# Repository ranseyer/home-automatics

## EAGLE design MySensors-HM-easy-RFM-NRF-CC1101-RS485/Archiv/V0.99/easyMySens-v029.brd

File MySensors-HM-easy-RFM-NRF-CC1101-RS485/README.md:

MySensors/HM easyPCB 

Communication via 
1) RFM69(H)W (868MHz and "W" Version recomended "HW" is not for all countries...), or 
2) CC1101 (868MHz for HomeMatic Protocol) 
3) NRF2401 (for mySensors 2,4 GHz) 
4) RS485 with Max487 for MySensors or Homematic Wired 

Connectors for 
1) N-Module Extensions 
2) Homematic-Universal PCB from Papa 
3) Grove Connectors but in 2,54mm raster 
4) Connector for screws or clamping 
5) more Sensors (I2C or Digital pin with Interupt) 
6) ATSHA204 (SMD solder)
 
Power via 
1) Step-Up 
2) Step-Down ("mini360")
3) Linear-Regulator 

Case 
1) Box2252
2) 59x65 (China Noname)
3) 67x98 (China Noname)
Many options with many drills 

Status 
Alpha, not tested. 

Important Hint:

Most Parts are optional. Use only what you need!

Changes / Known Bugs: 
-V01: 1 last-minute connection to "opt" header not knowingly not routed

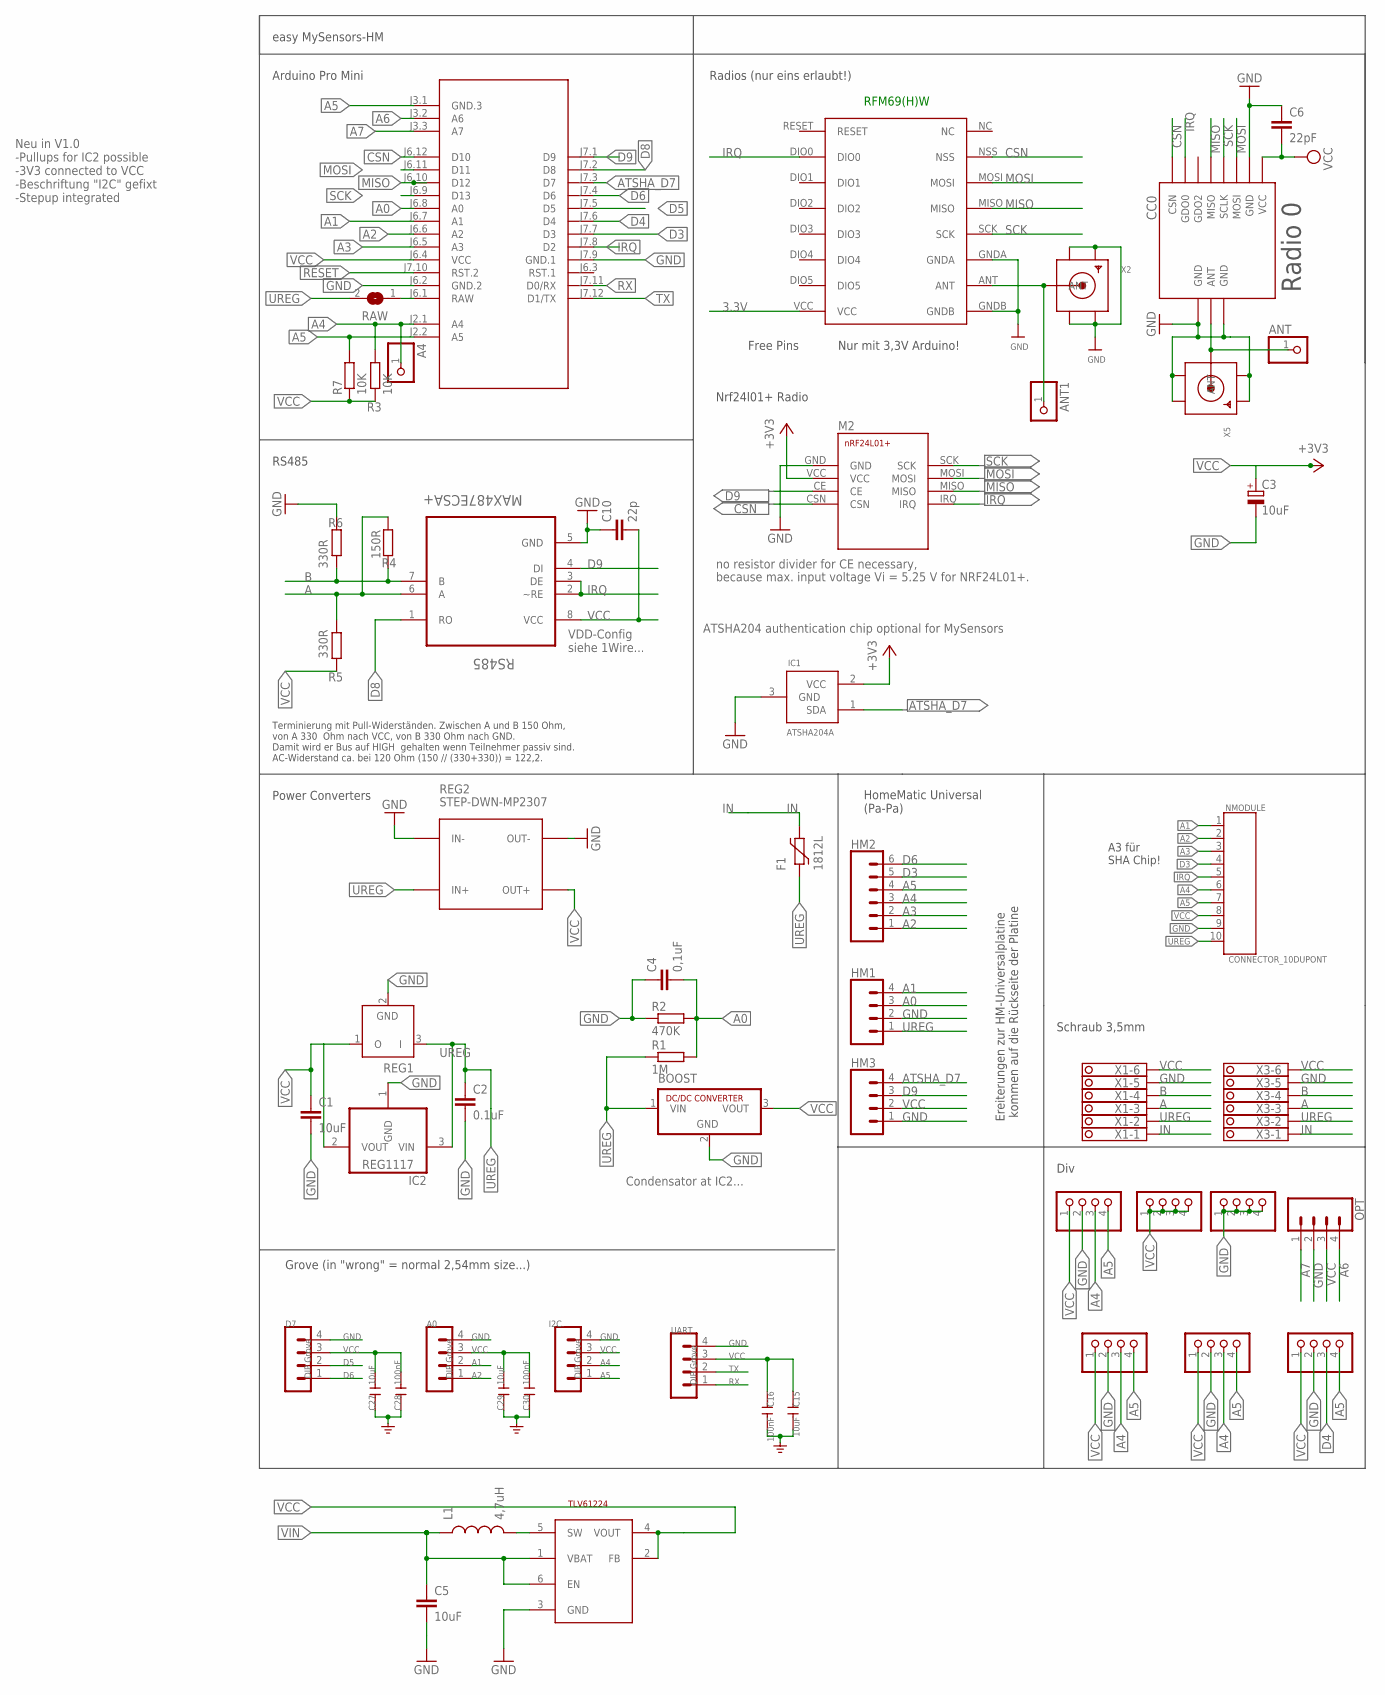
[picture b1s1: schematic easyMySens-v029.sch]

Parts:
A0: DIP Grove; MA04-1
A4: PINHD-1X1; 1X01
ANT, ANT1: PINHD-1X1; 1X01
BH1750: PINHD-1X04_2.54-S; 1X04-S
BOOST: R-78C1.8-1.0; SIP3
C1: 10uF; C1210
C2: 0.1uF; C1206
C3: 10uF; SMC_C
C4: 0,1uF; C1206
C5: 10uF; 0805
C6: 22pF; C0805
C10: 22p; C0805
C15, C27, C29: 10uF; C0603
C16, C28, C30: 100nF; C0603
CC0: CC1101; CC1101_MODULE1_SMD
D7: DIP Grove; MA04-1
F1: 1812L
HM1, HM3: CONN_04; 1X04
HM2: CONN_06SILK_FEMALE_PTH; 1X06
I2C-1, I2C-2: PINHD-1X04_2.54-S; 1X04-S
I2C.: DIP Grove; MA04-1
IC1: ATSHA204A; SOT23
IC2: REG1117; SOT223
JP1, JP3: PINHD-1X04_2.54-S; 1X04-S
L1: 4,7uH; 0805
M1: ARDUINO-PRO-MINI-3.3V#NP; ARDUINO-PRO-MINI#NP
M2: NRF24L01+SMD
MOTION: PINHD-1X04_2.54-S; 1X04-S
NMODULE: CONNECTOR_10DUPONT; DUPONT_10
OPT: CONN_04; 1X04
R1: 1M; R0805
R2: 470K; R0805
R3, R7: 10K; R0805
R4: 150R; R0805
R5, R6: 330R; R0805
RAW: SJ
REG1: LP2950Z; TO92
REG2: STEP-DWN-MP2307; DC-DC-STEP-DOWN-MP2307
RFM69W: RFM69HW; RFM
RS485: MAX487ECSA+; SOIC127P600X175-8N
STEPUP: TLV61224; SOT23-6L
UART: DIP Grove; MA04-1
X1, X3: 1751280
X2, X5: SMACONNECTOR_EDGE; SMA_EDGELAUNCH

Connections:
3.3V: IC1.2 (VCC), M2.VCC, RFM69W.VCC
A: R4.1, R5.2, RS485.6 (A), X1.3, X3.3
A0: C4.2, HM1.3, M1.J6.8 (A0), R1.2, R2.2
A1: A0.2, HM1.4, M1.J6.7 (A1), NMODULE.1
A2: A0.1, HM2.1, M1.J6.6 (A2), NMODULE.2
A3: HM2.2, M1.J6.5 (A3), NMODULE.3
A4: A4.1, BH1750.3, HM2.3, I2C-1.3, I2C-2.3, I2C..2, M1.J2.1 (A4), NMODULE.6, R3.2
A5: BH1750.4, HM2.4, I2C-1.4, I2C-2.4, I2C..1, M1.J2.2 (A5), M1.J3.1 (GND.3), MOTION.4, NMODULE.7, R7.2
A6: M1.J3.2 (A6), OPT.4
A7: M1.J3.3 (A7), OPT.1
ANT0: ANT.1, CC0.ANT, X5.P (ANT)
ATSHA_D7: HM3.4, IC1.1 (SDA), M1.J7.3 (D7)
B: R4.2, R6.1, RS485.7 (B), X1.4, X3.4
CSN: CC0.CSN, M1.J6.12 (D10), M2.CSN, RFM69W.NSS
D3: HM2.5, M1.J7.7 (D3), NMODULE.4
D4: M1.J7.6 (D4), MOTION.3
D5: D7.2, M1.J7.5 (D5)
D6: D7.1, HM2.6, M1.J7.4 (D6)
D8: M1.J7.2 (D8), RS485.1 (RO)
D9: HM3.3, M1.J7.1 (D9), M2.CE, RS485.4 (DI)
GND: A0.4, BH1750.2, BOOST.2 (GND), C1.2, C2.2, C3.-, C4.1, C5.2, C6.1, C10.1, C15.1, C16.1, C27.2, C28.2, C29.2, C30.2, CC0.GND@0 (GND), CC0.GND@1 (GND), CC0.GND@2 (GND), D7.4, HM1.2, HM3.1, I2C-1.2, I2C-2.2, I2C..4, IC1.3 (GND), IC2.1 (GND), JP1.1, JP1.2, JP1.3, JP1.4, M1.J6.2 (GND.2), M1.J7.9 (GND.1), M2.GND, MOTION.2, NMODULE.9, OPT.2, R2.1, R6.2, REG1.2 (GND), REG2.IN-, REG2.OUT-, RFM69W.GNDA, RFM69W.GNDB, RS485.5 (GND), STEPUP.3 (GND), UART.4, X1.5, X2.GND@1 (GND4), X2.GND@2 (GND3), X2.GND@3 (GND2), X2.GND@4 (GND1), X3.5, X5.GND@1 (GND4), X5.GND@2 (GND3), X5.GND@3 (GND2), X5.GND@4 (GND1)
IN: F1.P$2 (2), X1.1, X3.1
IRQ: CC0.GDO0, M1.J7.8 (D2), M2.IRQ, NMODULE.5, RFM69W.DIO0, RS485.2 (~RE), RS485.3 (DE)
MISO: CC0.MISO, M1.J6.10 (D12), M2.MISO, RFM69W.MISO
MOSI: CC0.MOSI, M1.J6.11 (D11), M2.MOSI, RFM69W.MOSI
unnamed: L1.2, STEPUP.5 (SW)
unnamed: ANT1.1, RFM69W.ANT, X2.P (ANT)
RAW: M1.J6.1 (RAW), RAW.1
RESET: M1.J7.10 (RST.2)
RX: M1.J7.11 (D0/RX), UART.1
SCK: CC0.SCLK, M1.J6.9 (D13), M2.SCK, RFM69W.SCK
TX: M1.J7.12 (D1/TX), UART.2
UREG: BOOST.1 (VIN), C2.1, F1.P$1 (1), HM1.1, IC2.3 (VIN), NMODULE.10, R1.1, RAW.2, REG1.3 (I), REG2.IN+, X1.2, X3.2
VCC: A0.3, BH1750.1, BOOST.3 (VOUT), C1.1, C3.+, C6.2, C10.2, C15.2, C16.2, C27.1, C28.1, C29.1, C30.1, CC0.VCC, D7.3, HM3.2, I2C-1.1, I2C-2.1, I2C..3, IC2.2 (VOUT), JP3.1, JP3.2, JP3.3, JP3.4, M1.J6.4 (VCC), MOTION.1, NMODULE.8, OPT.3, R3.1, R5.1, R7.1, REG1.1 (O), REG2.OUT+, RS485.8 (VCC), STEPUP.2 (FB), STEPUP.4 (VOUT), UART.3, X1.6, X3.6
VIN: C5.1, L1.1, STEPUP.1 (VBAT), STEPUP.6 (EN)

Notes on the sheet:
easy MySensors-HM
Arduino Pro Mini
Free Pins
Nrf24l01+ Radio
Power Converters
RS485
VDD-Config siehe 1Wire...
no resistor divider for CE necessary,
because max. input voltage Vi = 5.25 V for NRF24L01+.
ATSHA204 authentication chip optional for MySensors
RFM69(H)W
Nur mit 3,3V Arduino!
Radio 0
Terminierung mit Pull-Widerständen. Zwischen A und B 150 Ohm, von A 330 Ohm nach VCC, von B 330 Ohm nach GND. Damit wird er Bus auf HIGH gehalten wenn Teilnehmer passiv sind. AC-Widerstand ca. bei 120 Ohm (150 // (330+330)) = 122,2.
A3 für SHA Chip!
Ereiterungen zur HM-Universalplatine kommen auf die Rückseite der Platine
Condensator at IC2...
HomeMatic Universal (Pa-Pa)
Schraub 3,5mm
Div
Radios (nur eins erlaubt!)
Grove (in "wrong" = normal 2,54mm size...)
Neu in V1.0 -Pullups for IC2 possible -3V3 connected to VCC -Beschriftung "I2C" gefixt -Stepup integrated

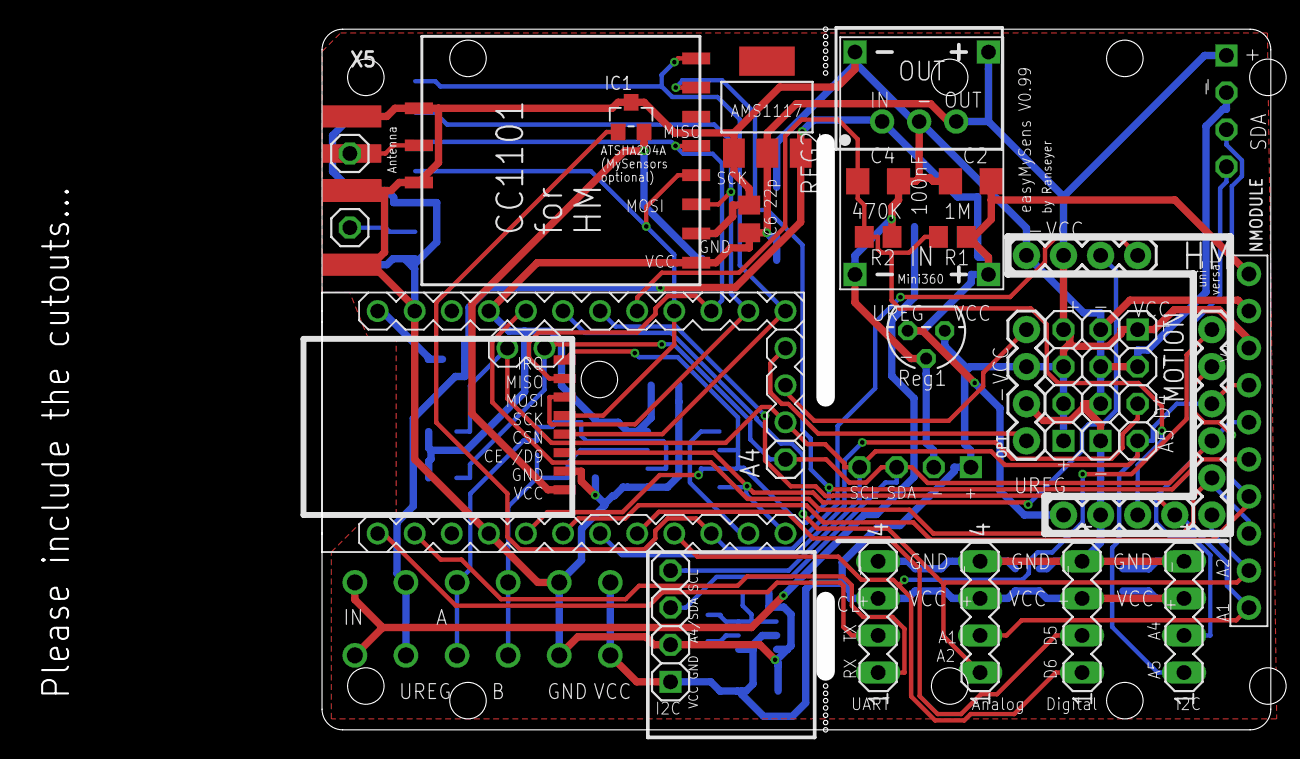
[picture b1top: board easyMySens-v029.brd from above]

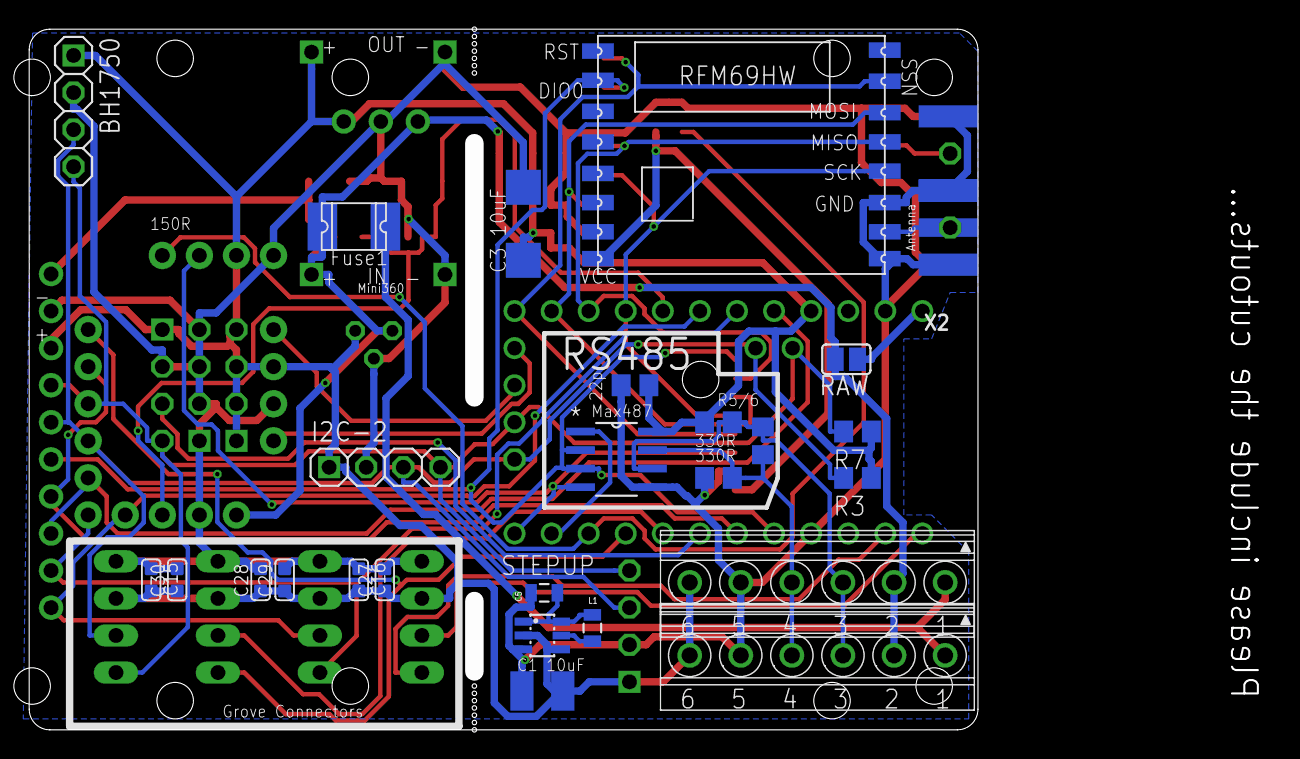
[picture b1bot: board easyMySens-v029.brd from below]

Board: 2 copper layers, 65.0 x 48.0 mm, 56 parts (26 on the bottom side), 34 nets.

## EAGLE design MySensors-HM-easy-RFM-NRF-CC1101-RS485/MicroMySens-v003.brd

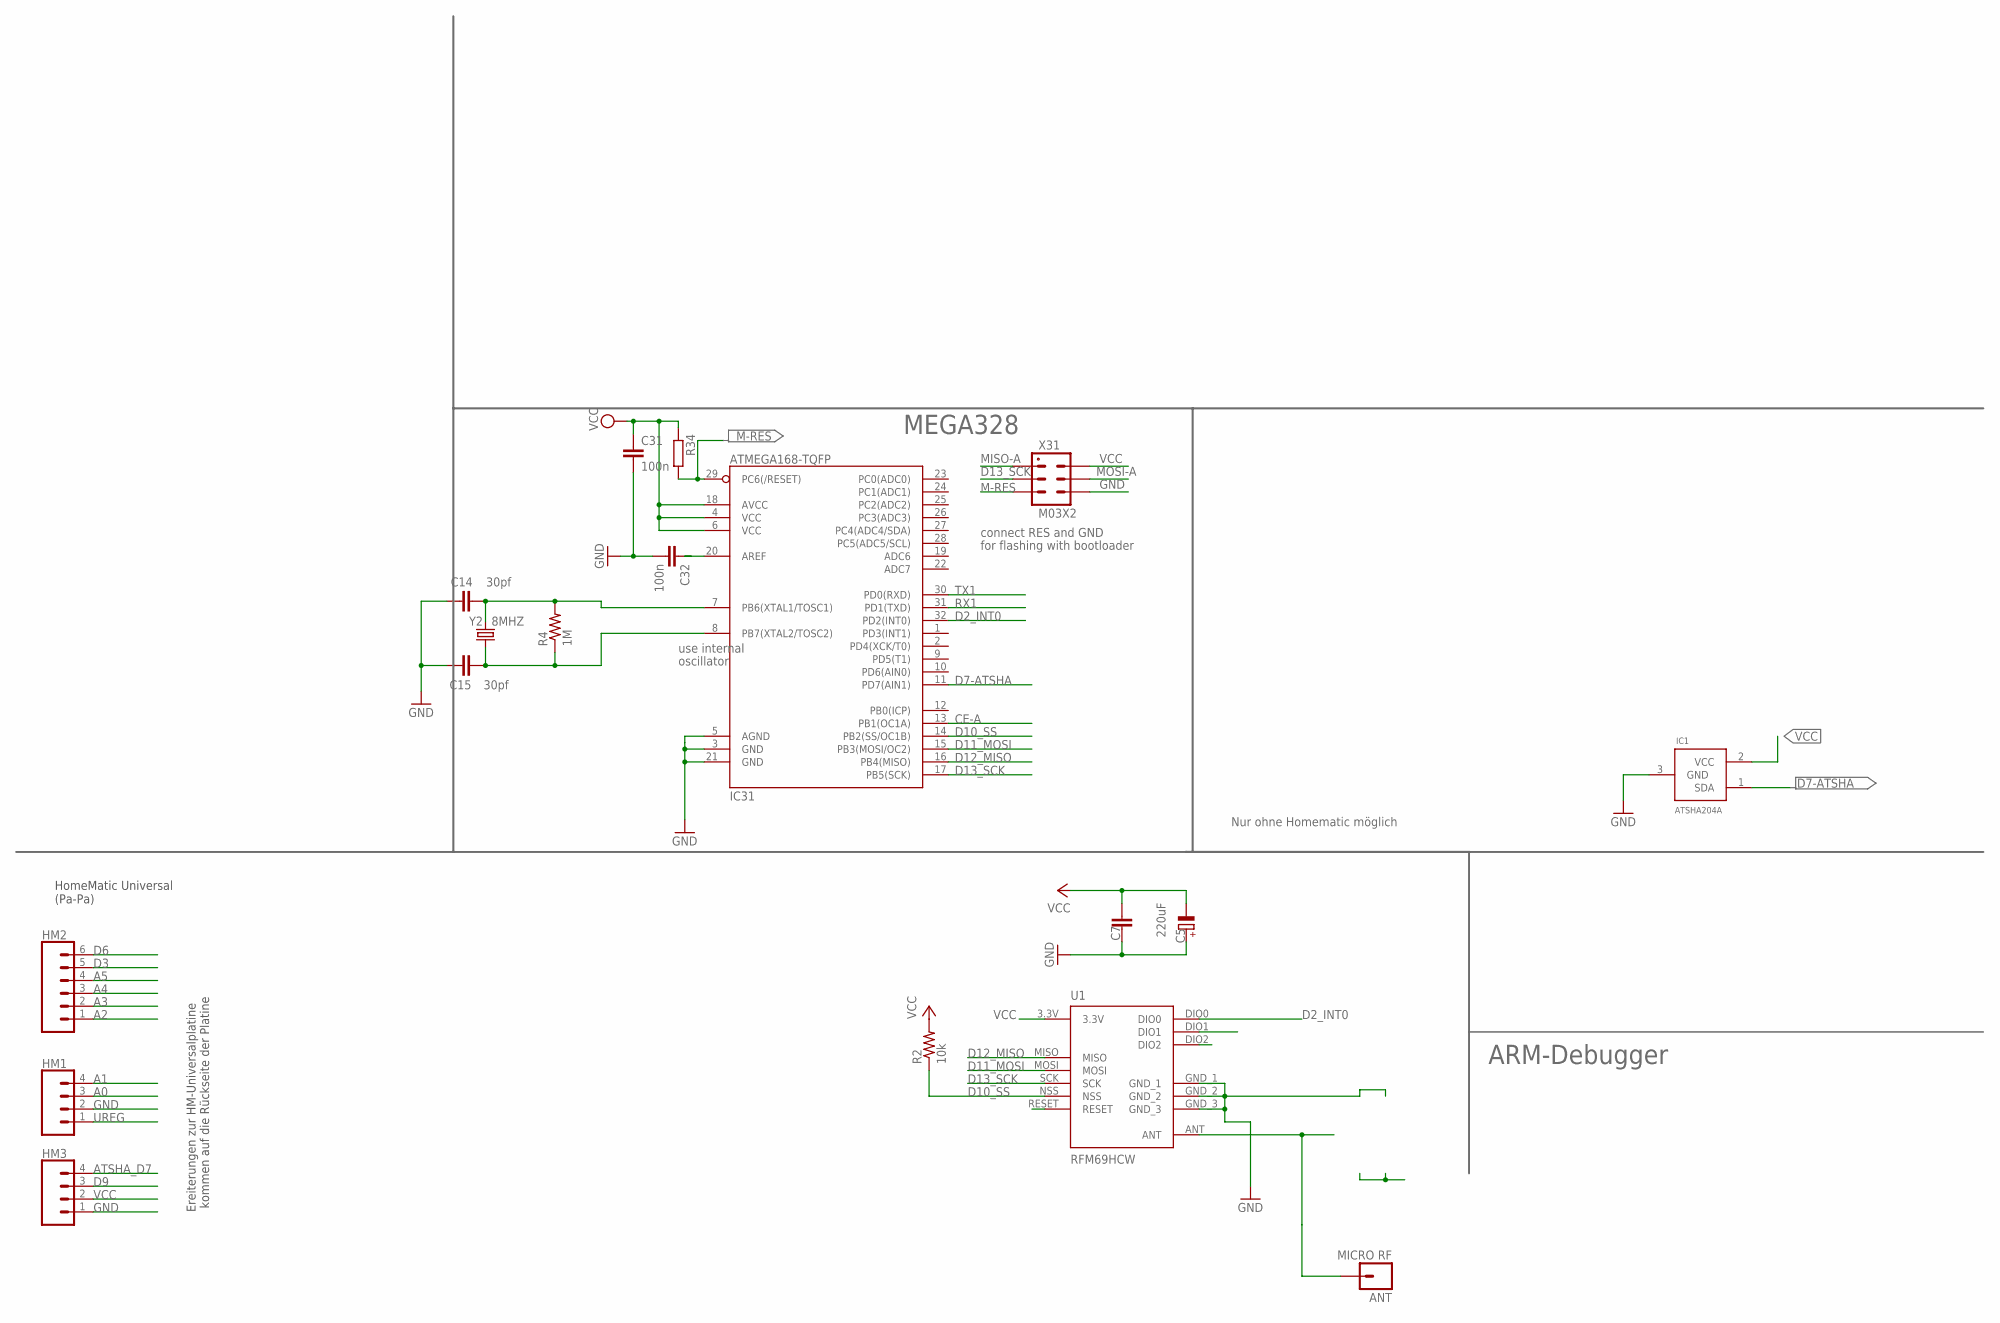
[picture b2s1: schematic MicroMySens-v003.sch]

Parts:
ANT: MICRO RF; 1X01
C5: 220uF; E5-8,5
C7: C-EUC1812; C1812
C14, C15: 30pf; 0805
C31, C32: 100n; C0805
HM1, HM3: CONN_04; 1X04
HM2: CONN_06SILK_FEMALE_PTH; 1X06
IC1: ATSHA204A; SOT23
IC31: ATMEGA168-TQFP; TQFP32-08
R2: 10k; 0805
R4: 1M; 0805
R34: R-EU_R0805; R0805
U1: RFM69HCW; RFM69HCW-XXXS2
X31: M03X2; 2X03-1.27MM_SMD
Y2: 8MHZ; CRYSTAL-TXC-7A

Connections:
A0: HM1.3
A1: HM1.4
A2: HM2.1
A3: HM2.2
A4: HM2.3
A5: HM2.4
ANT: ANT.1, U1.ANT
ATSHA_D7: HM3.4
CE-A: IC31.13 (PB1(OC1A))
D2_INT0: IC31.32 (PD2(INT0)), U1.DIO0
D3: HM2.5
D6: HM2.6
D7-ATSHA: IC1.1 (SDA), IC31.11 (PD7(AIN1))
D9: HM3.3
D10_SS: IC31.14 (PB2(SS/OC1B)), R2.1, U1.NSS
D11_MOSI: IC31.15 (PB3(MOSI/OC2)), U1.MOSI
D12_MISO: IC31.16 (PB4(MISO)), U1.MISO
D13_SCK: IC31.17 (PB5(SCK)), U1.SCK, X31.P$3 (3)
GND: C5.+, C7.2, C14.1, C15.1, C31.2, C32.2, HM1.2, HM3.1, IC1.3 (GND), IC31.3 (GND), IC31.5 (AGND), IC31.21 (GND), U1.GND_1, U1.GND_2, U1.GND_3, X31.P$6 (6)
M-RES: IC31.29 (PC6(/RESET)), R34.2, X31.P$5 (5)
MISO-A: X31.P$1 (1)
MOSI-A: X31.P$4 (4)
unnamed: C14.2, IC31.7 (PB6(XTAL1/TOSC1)), R4.2, Y2.P$2 (2)
unnamed: C32.1, IC31.20 (AREF)
unnamed: C15.2, IC31.8 (PB7(XTAL2/TOSC2)), R4.1, Y2.P$1 (1)
RX1: IC31.31 (PD1(TXD))
TX1: IC31.30 (PD0(RXD))
UREG: HM1.1
VCC: C5.-, C7.1, C31.1, HM3.2, IC1.2 (VCC), IC31.4 (VCC), IC31.6 (VCC), IC31.18 (AVCC), R2.2, R34.1, U1.3.3V, X31.P$2 (2)

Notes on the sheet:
MEGA328
ARM-Debugger
use internal
oscillator
connect RES and GND
for flashing with bootloader
Nur ohne Homematic möglich
Ereiterungen zur HM-Universalplatine kommen auf die Rückseite der Platine
HomeMatic Universal (Pa-Pa)

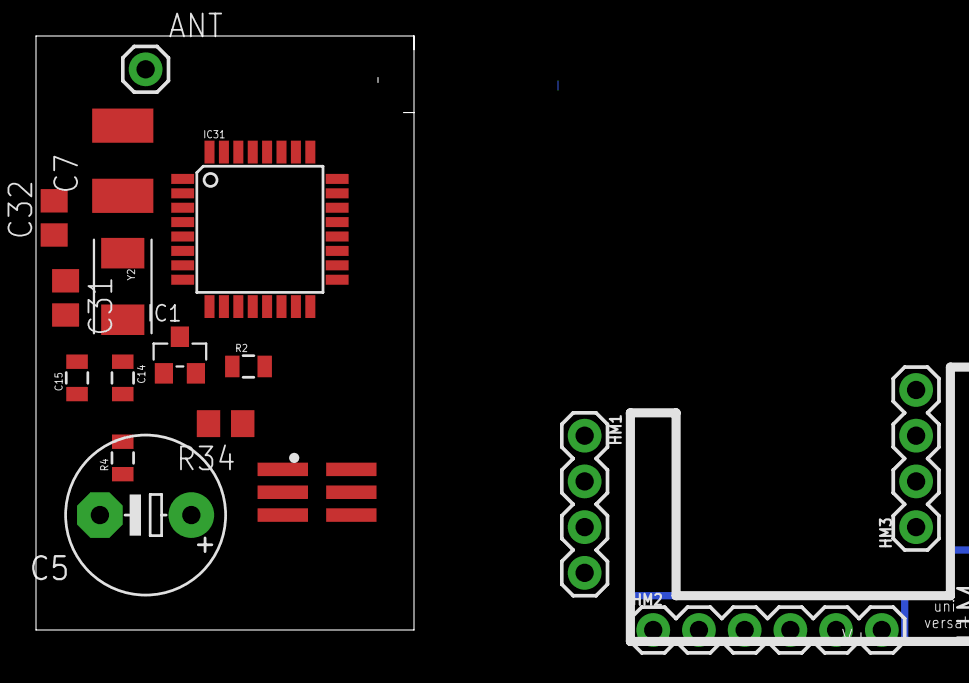
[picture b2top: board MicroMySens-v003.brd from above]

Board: 2 copper layers, 21.0 x 33.0 mm, 18 parts (1 on the bottom side), 13 nets.

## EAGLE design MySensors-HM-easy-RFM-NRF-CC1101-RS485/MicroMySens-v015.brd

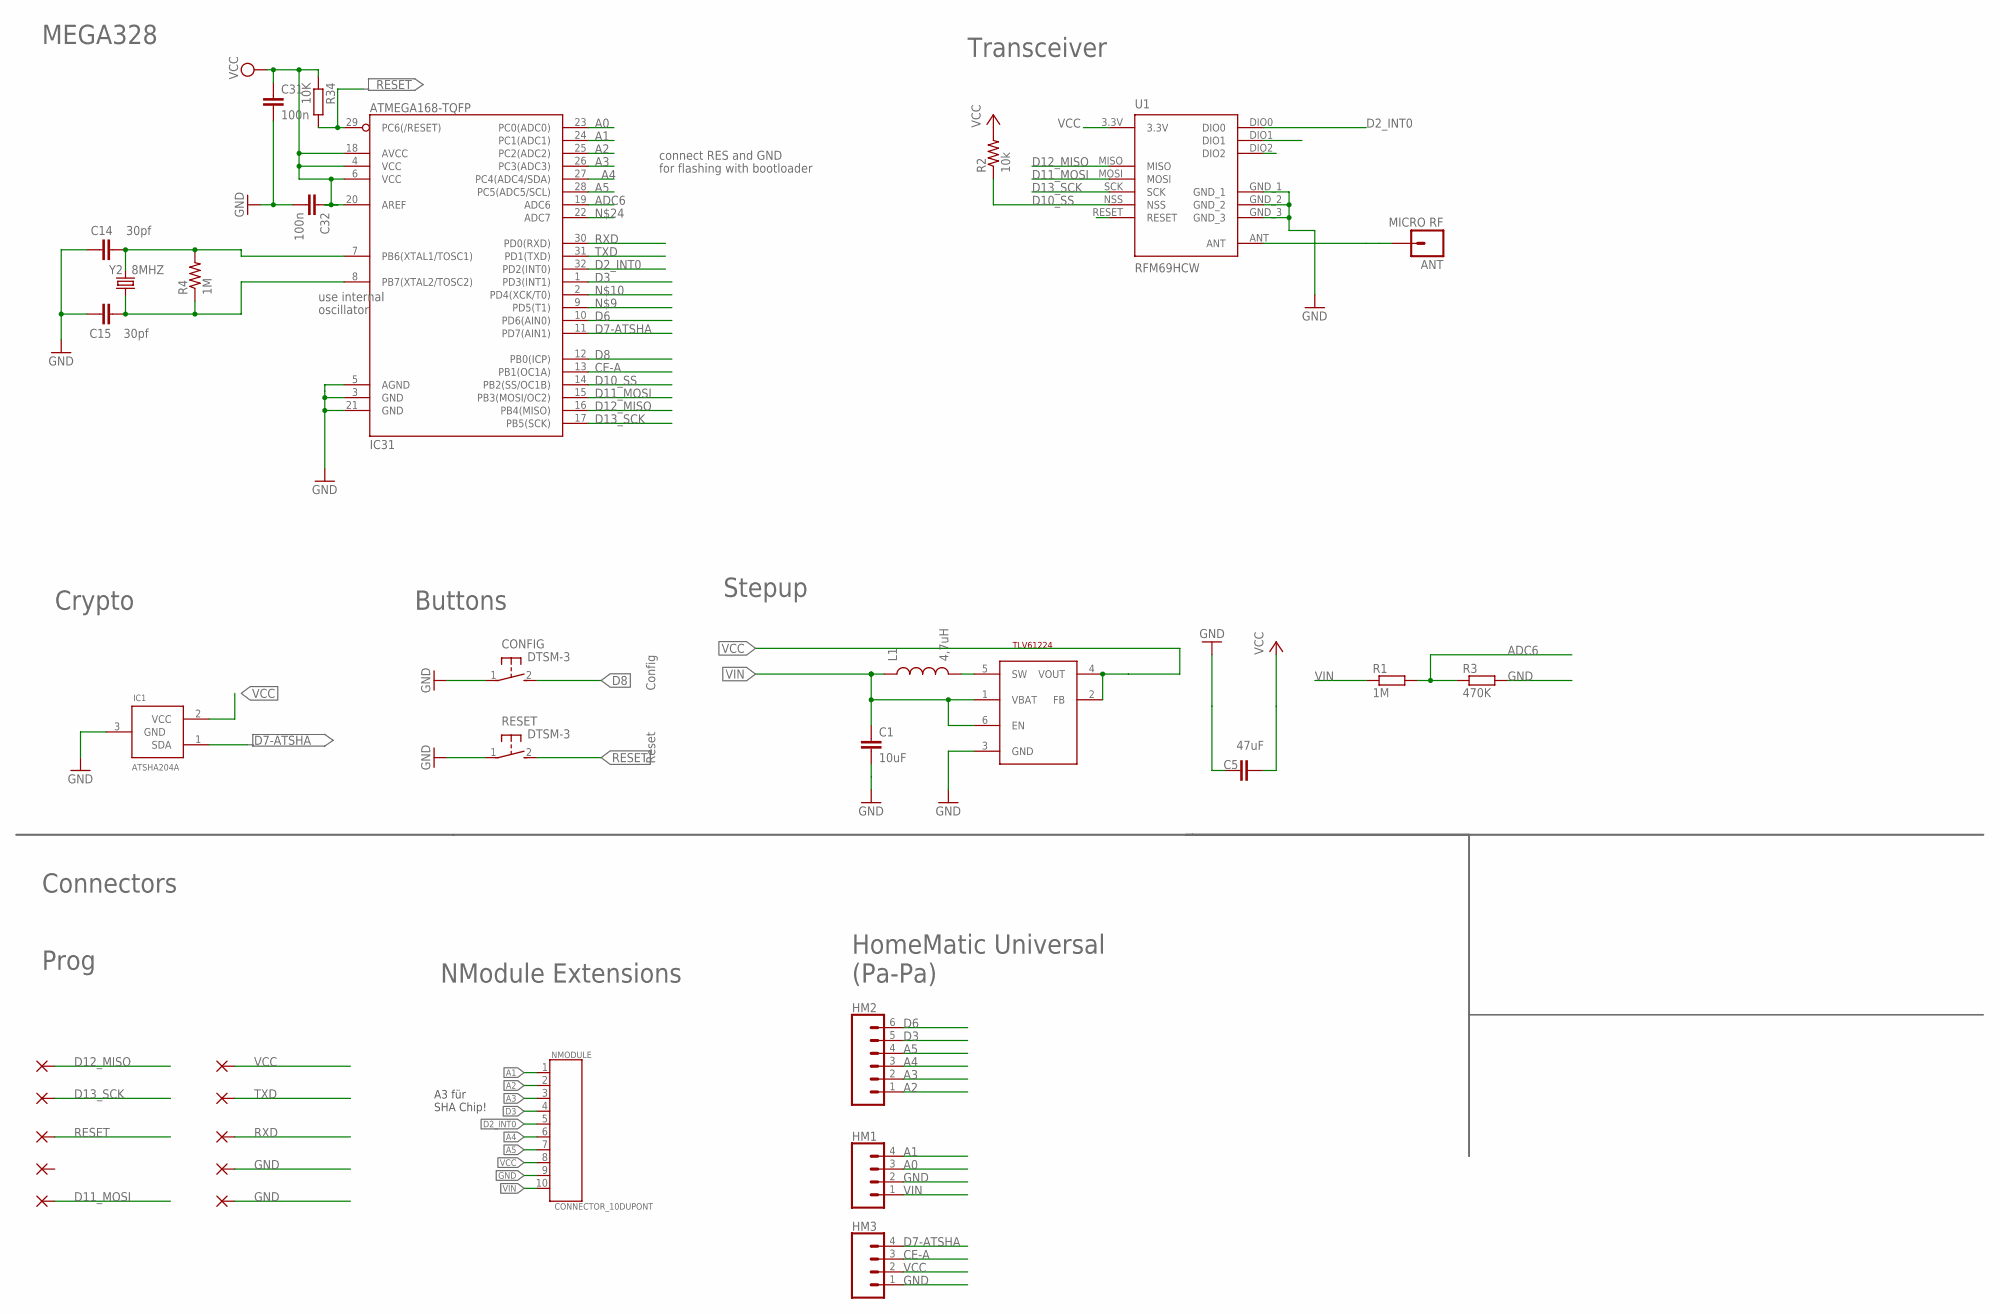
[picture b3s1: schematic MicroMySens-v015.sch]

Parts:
ANT: MICRO RF; 1X01
C1: 10uF; 0805
C5: 47uF; C1210
C14, C15: 30pf; 0805
C31, C32: 100n; C0805
CONFIG: DTSM-3
GND, GND2: WIREPADSMD1,27-254; SMD1,27-2,54
HM1, HM3: CONN_04; 1X04
HM2: CONN_06SILK_FEMALE_PTH; 1X06
IC1: ATSHA204A; SOT23
IC31: ATMEGA168-TQFP; TQFP32-08
L1: 4,7uH; 0805
MISO: WIREPADSMD1,27-254; SMD1,27-2,54
MOSI: WIREPADSMD1,27-254; SMD1,27-2,54
NC: WIREPADSMD1,27-254; SMD1,27-2,54
NMODULE: CONNECTOR_10DUPONT; DUPONT_10
R1: 1M; R0805
R2: 10k; 0805
R3: 470K; R0805
R4: 1M; 0805
R34: 10K; R0805
RESET: DTSM-3
RST: WIREPADSMD1,27-254; SMD1,27-2,54
RXD: WIREPADSMD1,27-254; SMD1,27-2,54
SCK: WIREPADSMD1,27-254; SMD1,27-2,54
STEPUP: TLV61224; SOT23-6L
TXD: WIREPADSMD1,27-254; SMD1,27-2,54
U1: RFM69HCW; RFM69HCW-XXXS2
VCC: WIREPADSMD1,27-254; SMD1,27-2,54
Y2: 8MHZ; CRYSTAL-TXC-7A

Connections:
A0: HM1.3, IC31.23 (PC0(ADC0))
A1: HM1.4, IC31.24 (PC1(ADC1)), NMODULE.1
A2: HM2.1, IC31.25 (PC2(ADC2)), NMODULE.2
A3: HM2.2, IC31.26 (PC3(ADC3)), NMODULE.3
A4: HM2.3, IC31.27 (PC4(ADC4/SDA)), NMODULE.6
A5: HM2.4, IC31.28 (PC5(ADC5/SCL)), NMODULE.7
ADC6: IC31.19 (ADC6), R1.2, R3.1
ANT: ANT.1, U1.ANT
CE-A: HM3.3, IC31.13 (PB1(OC1A))
D2_INT0: IC31.32 (PD2(INT0)), NMODULE.5, U1.DIO0
D3: HM2.5, IC31.1 (PD3(INT1)), NMODULE.4
D6: HM2.6, IC31.10 (PD6(AIN0))
D7-ATSHA: HM3.4, IC1.1 (SDA), IC31.11 (PD7(AIN1))
D8: CONFIG.2, IC31.12 (PB0(ICP))
D10_SS: IC31.14 (PB2(SS/OC1B)), R2.1, U1.NSS
D11_MOSI: IC31.15 (PB3(MOSI/OC2)), MOSI.1, U1.MOSI
D12_MISO: IC31.16 (PB4(MISO)), MISO.1, U1.MISO
D13_SCK: IC31.17 (PB5(SCK)), SCK.1, U1.SCK
GND: C1.2, C5.1, C14.1, C15.1, C31.2, C32.2, CONFIG.1, GND.1, GND2.1, HM1.2, HM3.1, IC1.3 (GND), IC31.3 (GND), IC31.5 (AGND), IC31.21 (GND), NMODULE.9, R3.2, RESET.1, STEPUP.3 (GND), U1.GND_1, U1.GND_2, U1.GND_3
unnamed: C14.2, IC31.7 (PB6(XTAL1/TOSC1)), R4.2, Y2.P$2 (2)
unnamed: L1.2, STEPUP.5 (SW)
unnamed: C15.2, IC31.8 (PB7(XTAL2/TOSC2)), R4.1, Y2.P$1 (1)
RESET: IC31.29 (PC6(/RESET)), R34.2, RESET.2, RST.1
RXD: IC31.30 (PD0(RXD)), RXD.1
TXD: IC31.31 (PD1(TXD)), TXD.1
VCC: C5.2, C31.1, C32.1, HM3.2, IC1.2 (VCC), IC31.4 (VCC), IC31.6 (VCC), IC31.18 (AVCC), IC31.20 (AREF), NMODULE.8, R2.2, R34.1, STEPUP.2 (FB), STEPUP.4 (VOUT), U1.3.3V, VCC.1
VIN: C1.1, HM1.1, L1.1, NMODULE.10, R1.1, STEPUP.1 (VBAT), STEPUP.6 (EN)

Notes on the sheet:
MEGA328
use internal
oscillator
connect RES and GND
for flashing with bootloader
A3 für SHA Chip!
Config
Reset
Crypto
Buttons
Stepup
Transceiver
Connectors
Prog
NModule Extensions
HomeMatic Universal (Pa-Pa)

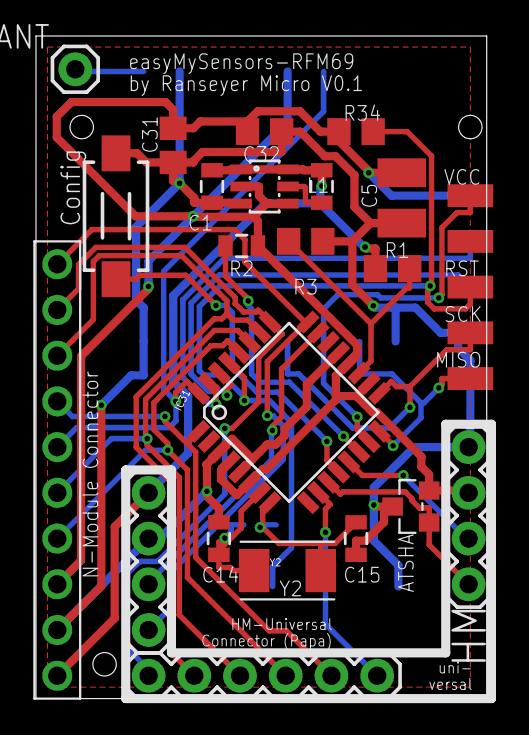
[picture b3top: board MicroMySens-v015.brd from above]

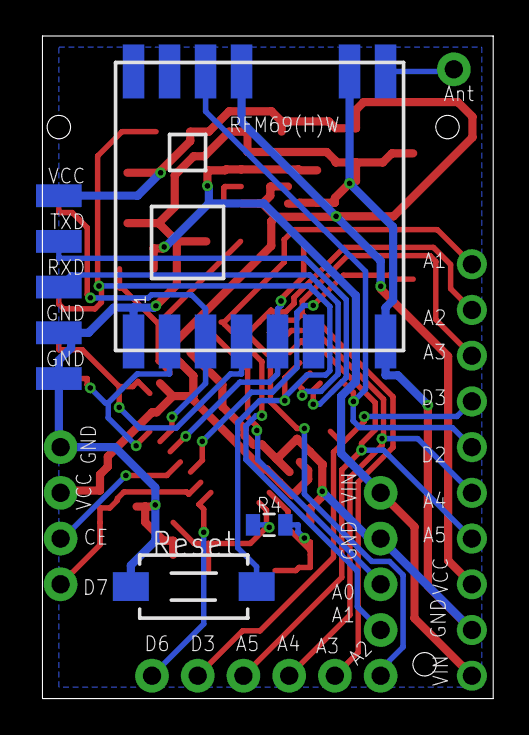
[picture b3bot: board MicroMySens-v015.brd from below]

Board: 2 copper layers, 25.0 x 36.8 mm, 34 parts (8 on the bottom side), 27 nets.

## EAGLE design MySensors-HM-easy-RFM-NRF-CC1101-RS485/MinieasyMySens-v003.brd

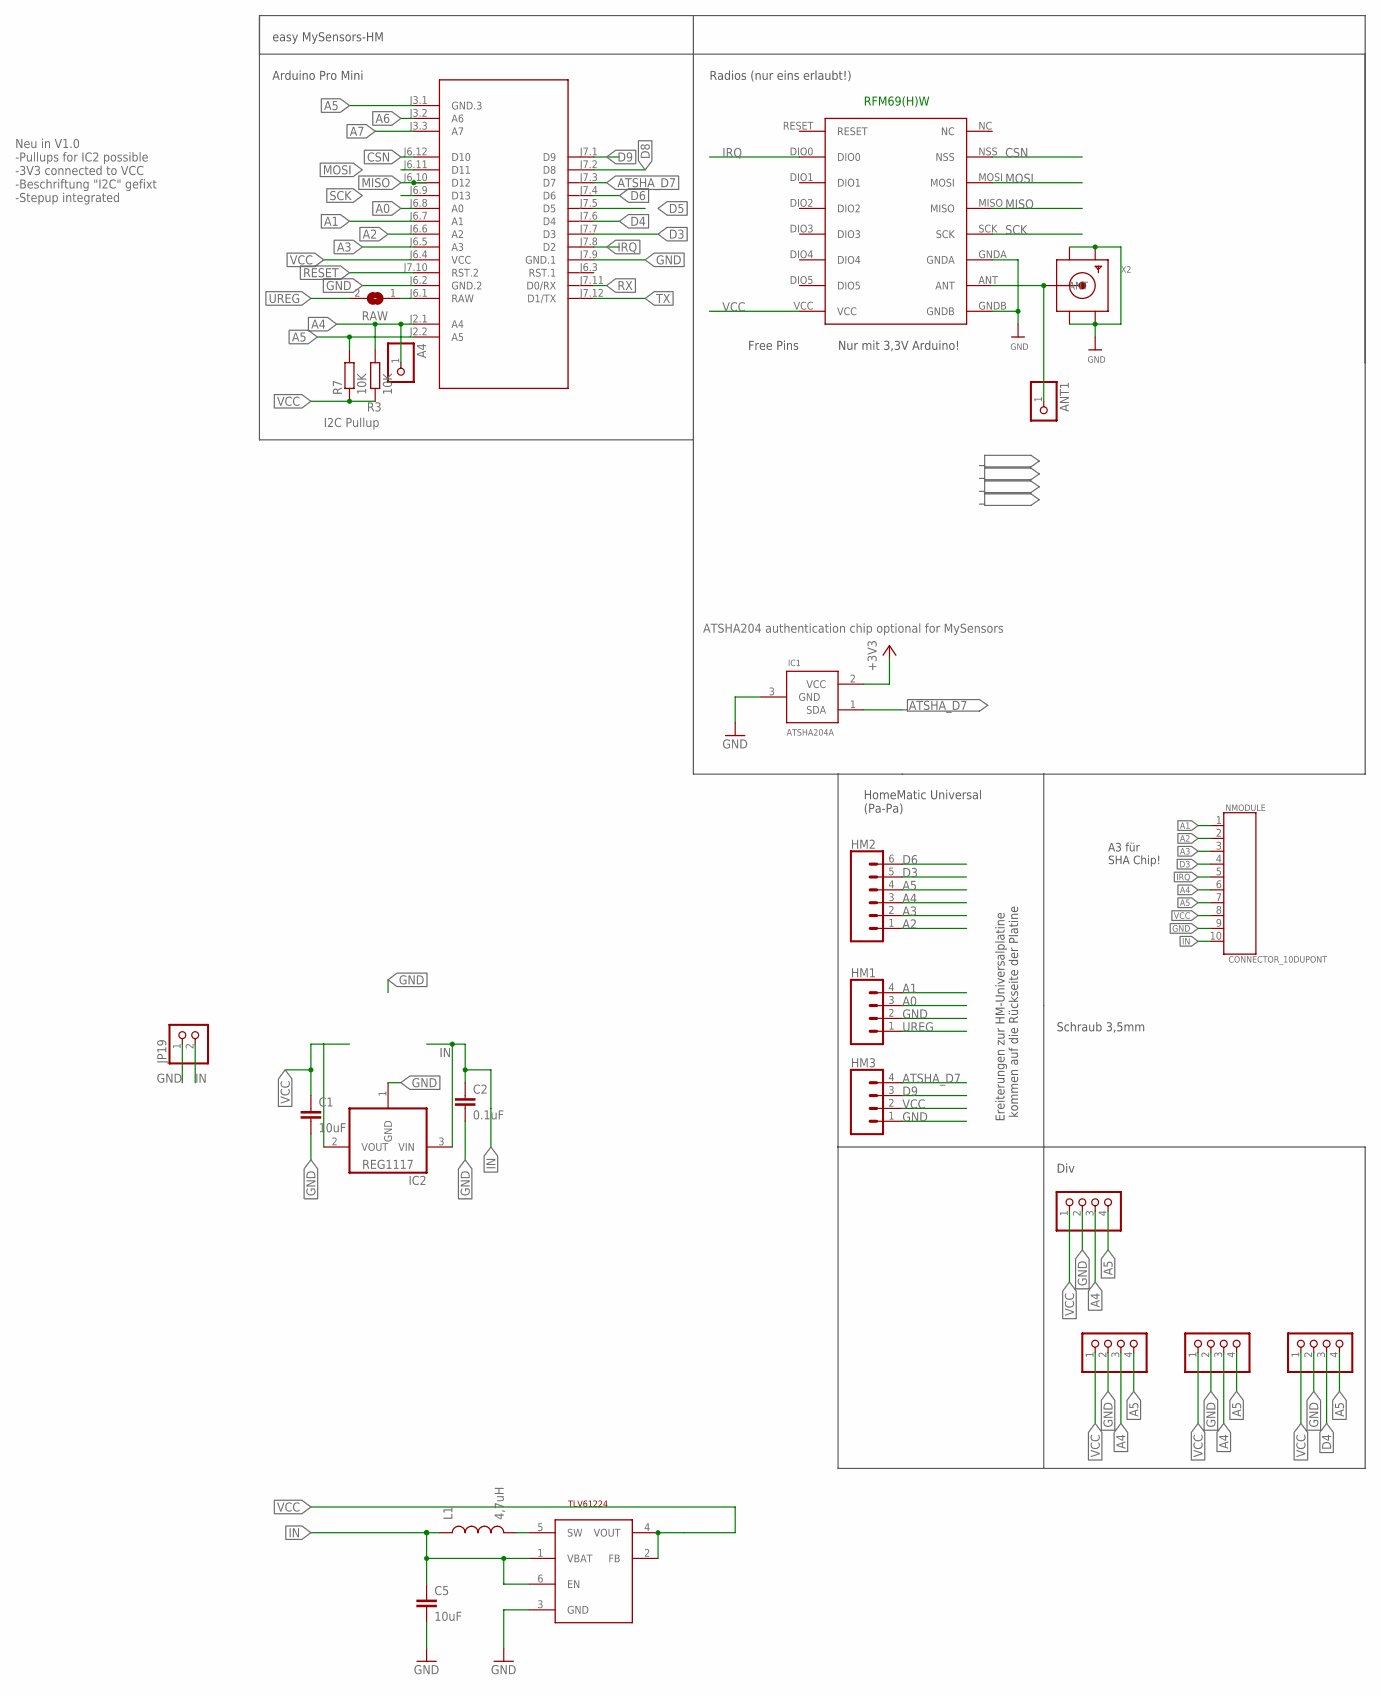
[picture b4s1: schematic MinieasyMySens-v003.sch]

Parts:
A4: PINHD-1X1; 1X01
ANT1: PINHD-1X1; 1X01
BH1750: PINHD-1X04_2.54-S; 1X04-S
C1: 10uF; C1210
C2: 0.1uF; C1206
C5: 10uF; 0805
HM1, HM3: CONN_04; 1X04
HM2: CONN_06SILK_FEMALE_PTH; 1X06
I2C-1, I2C-2: PINHD-1X04_2.54-S; 1X04-S
IC1: ATSHA204A; SOT23
IC2: REG1117; SOT223
JP19: PINHD-1X2; 1X02
L1: 4,7uH; 0805
M1: ARDUINO-PRO-MINI-3.3V#NP; ARDUINO-PRO-MINI#NP
MOTION: PINHD-1X04_2.54-S; 1X04-S
NMODULE: CONNECTOR_10DUPONT; DUPONT_10
R3, R7: 10K; R0805
RAW: SJ
RFM69W: RFM69HW; RFM
STEPUP: TLV61224; SOT23-6L
X2: SMACONNECTOR_EDGE; SMA_EDGELAUNCH

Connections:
A0: HM1.3, M1.J6.8 (A0)
A1: HM1.4, M1.J6.7 (A1), NMODULE.1
A2: HM2.1, M1.J6.6 (A2), NMODULE.2
A3: HM2.2, M1.J6.5 (A3), NMODULE.3
A4: A4.1, BH1750.3, HM2.3, I2C-1.3, I2C-2.3, M1.J2.1 (A4), NMODULE.6, R3.2
A5: BH1750.4, HM2.4, I2C-1.4, I2C-2.4, M1.J2.2 (A5), M1.J3.1 (GND.3), MOTION.4, NMODULE.7, R7.2
A6: M1.J3.2 (A6)
A7: M1.J3.3 (A7)
ATSHA_D7: HM3.4, IC1.1 (SDA), M1.J7.3 (D7)
CSN: M1.J6.12 (D10), RFM69W.NSS
D3: HM2.5, M1.J7.7 (D3), NMODULE.4
D4: M1.J7.6 (D4), MOTION.3
D5: M1.J7.5 (D5)
D6: HM2.6, M1.J7.4 (D6)
D8: M1.J7.2 (D8)
D9: HM3.3, M1.J7.1 (D9)
GND: BH1750.2, C1.2, C2.2, C5.2, HM1.2, HM3.1, I2C-1.2, I2C-2.2, IC1.3 (GND), IC2.1 (GND), JP19.1, M1.J6.2 (GND.2), M1.J7.9 (GND.1), MOTION.2, NMODULE.9, RFM69W.GNDA, RFM69W.GNDB, STEPUP.3 (GND), X2.GND@1 (GND4), X2.GND@2 (GND3), X2.GND@3 (GND2), X2.GND@4 (GND1)
IN: C2.1, C5.1, IC2.3 (VIN), JP19.2, L1.1, NMODULE.10, STEPUP.1 (VBAT), STEPUP.6 (EN)
IRQ: M1.J7.8 (D2), NMODULE.5, RFM69W.DIO0
MISO: M1.J6.10 (D12), RFM69W.MISO
MOSI: M1.J6.11 (D11), RFM69W.MOSI
unnamed: L1.2, STEPUP.5 (SW)
unnamed: ANT1.1, RFM69W.ANT, X2.P (ANT)
RAW: M1.J6.1 (RAW), RAW.1
RESET: M1.J7.10 (RST.2)
RX: M1.J7.11 (D0/RX)
SCK: M1.J6.9 (D13), RFM69W.SCK
TX: M1.J7.12 (D1/TX)
UREG: HM1.1, RAW.2
VCC: BH1750.1, C1.1, HM3.2, I2C-1.1, I2C-2.1, IC1.2 (VCC), IC2.2 (VOUT), M1.J6.4 (VCC), MOTION.1, NMODULE.8, R3.1, R7.1, RFM69W.VCC, STEPUP.2 (FB), STEPUP.4 (VOUT)

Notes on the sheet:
easy MySensors-HM
Arduino Pro Mini
Free Pins
ATSHA204 authentication chip optional for MySensors
RFM69(H)W
Nur mit 3,3V Arduino!
A3 für SHA Chip!
Ereiterungen zur HM-Universalplatine kommen auf die Rückseite der Platine
HomeMatic Universal (Pa-Pa)
Schraub 3,5mm
Div
Radios (nur eins erlaubt!)
Neu in V1.0 -Pullups for IC2 possible -3V3 connected to VCC -Beschriftung "I2C" gefixt -Stepup integrated
I2C Pullup

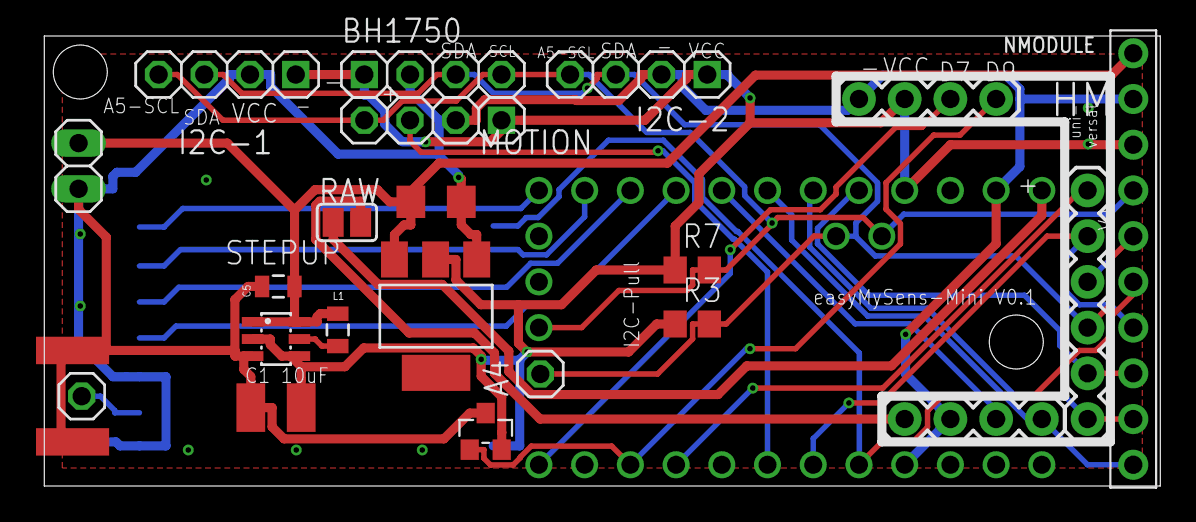
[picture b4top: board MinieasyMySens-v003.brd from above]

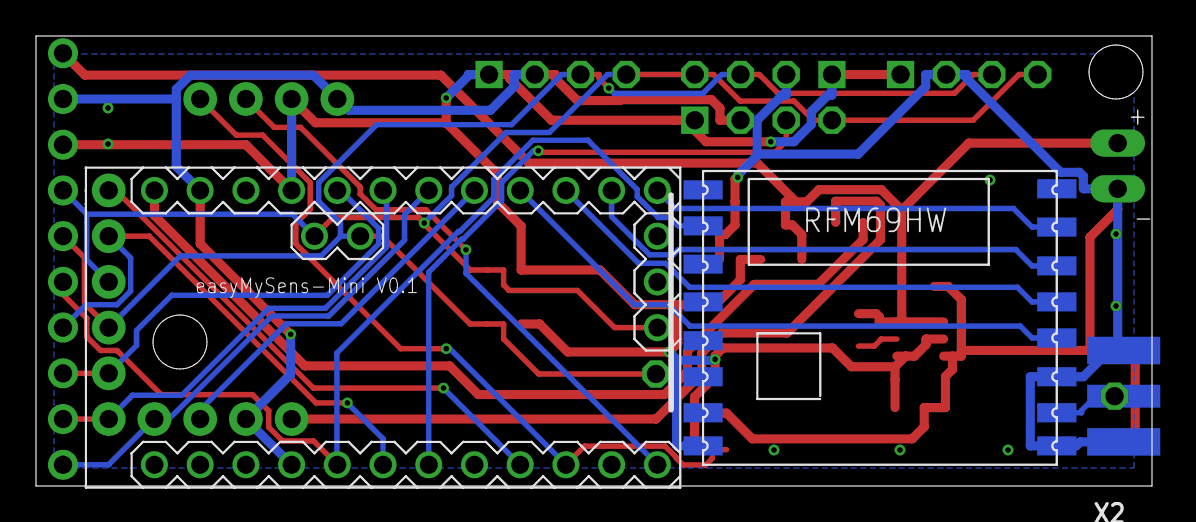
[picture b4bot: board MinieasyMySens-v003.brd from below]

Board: 2 copper layers, 62.0 x 25.0 mm, 24 parts (3 on the bottom side), 23 nets.

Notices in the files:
MySensors-easyRS485/design/MySens-easyRS485-v001.brd:
Licensed under
CERN OHL v.1.2
parts and their libraries:
diy-modules: Released under the Creative Commons Attribution 4.0 International License: http://creativecommons.org/licenses/by/4.0
SparkFun-Connectors: Licensing: Creative Commons ShareAlike 4.0 International - https://creativecommons.org/licenses/by-sa/4.0
